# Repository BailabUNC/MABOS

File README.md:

# MABOS
*All work in the MABOS repository is under Copyright Protections enumerated in the LICENSE file. Please contact Arjun Putcha - arjun22@live.unc.edu - for any questions related to redistribution of this work*

*Please see [fastplotlib](https://github.com/kushalkolar/fastplotlib/tree/master), developed by Kushal Kolar, to learn more about the plotting library we primarily use.

https://github.com/BailabUNC/MABOS/assets/96029511/e3c2583f-f5fd-4558-a8c5-83fa992f67cb

There are three key folders in this repository: full_design, firmware, and application.

## Full Design
This folder contains the *CAD* files (.sch and .brd) detailing schematic and layout of our pulse oximeter. It also contains a CAD library file - COMPONENTS_LIB.flbr - that has the relevant files for each component used in our design.

There is also a folder *Fab_Outputs* that contains the fabrication files necessary for laser cutting the top and bottom side of the board. *_autocad.dxf* files contain the file compatible with our laser cutter. Refer to *protocols/PCB_protocols.pdf* to follow our fabrication process.

Below is the schematic for our Infrared LED and Photodiode drivers; The 5-stage analog signal processing pipeline and led drivers are detailed in the schematic. The same schematic is used for the two other channels.

## Firmware
There are 3 directories in this folder: Arduino, Python, and zephyr_workspace.

### Arduino
Contains the .ino file used for the adafruit_itsybitsy_nrf52840 board. The code allows for the control of 3 LED channels and 3 ADC channels. Currently, the duty cycle is set to 50%, and the acquisition rate at 100 Hz.

We also take a burst sample of each ADC (currently 5 samples) to mitigate some noise, and implement a moving average filter with a window size of 10 samples to smooth the output data.

### Python
The code here will soon be removed.

### Zephyr Workspace
Contains the source code, build files, and modified board files to use the adafruit_itsybitsy_nrf52840 board. The board files are modified to configure 3 LED and 3 ADC channels. You can reference the readme file in *firmware/zephyr_workspace* for further details on modifications made.

## Application
The *utils* folder contains the core API used to acquire, plot, and save biosensor data in real time. The *PPG Widget* python notebook utilizes the core API to operate our device. When running this script, a file named *cache.sqlite3* will be created that contains all acquired data. For our uses, we've found a minute of data acquisition corresponds to ~1 MB of data saved.

The *GUI* folder contains a QT Desktop application used solely for displaying acquired biometrics, including SpO2, Heart Rate, Respiration Rate, and Epidermal Melanin Concentration.

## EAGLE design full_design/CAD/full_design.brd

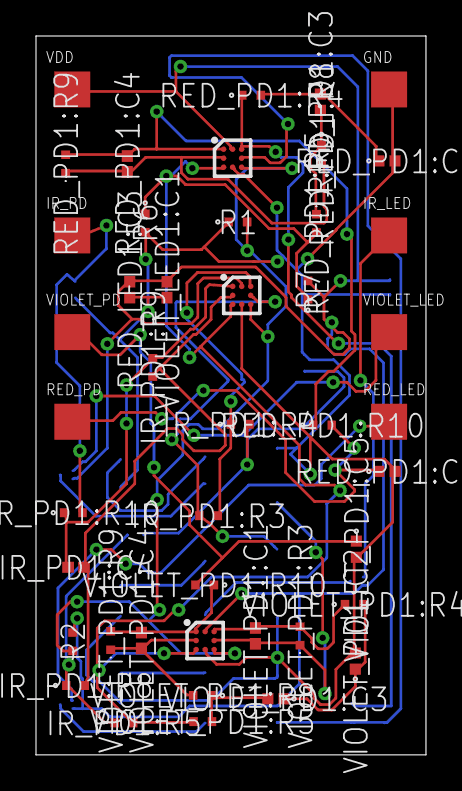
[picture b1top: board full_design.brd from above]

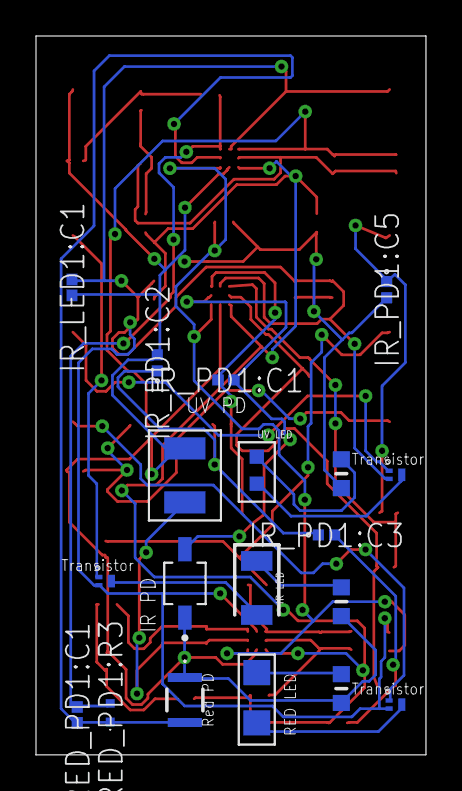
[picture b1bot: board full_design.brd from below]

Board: 2 copper layers, 21.7 x 39.9 mm, 63 parts (19 on the bottom side), 34 nets.

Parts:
GND: PAD
IR_LED: PAD
IR_LED1:C1: CAPACITOR-12PF; CAPC1005X55N
IR_LED1:LED1: IRLED; LEDC3216X180N
IR_LED1:Q1: TRANSISTOR; SOT883B
IR_LED1:R1: RESISTOR-100OHM; RESC1608X55N
IR_PD: PAD
IR_PD1:C1: CAPACITOR-270PF; CAPC1005X55N
IR_PD1:C2, IR_PD1:C5: CAPACITOR-10µF; C0402
IR_PD1:C3: CAPACITOR-3.3µF; C0402
IR_PD1:C4: CAPACITOR-5600PF; CAPC1005X55N
IR_PD1:D1: IRPD; XDCR_VEMD2023X01
IR_PD1:IC1: ADA4505-2; BGA8C50P3X3_142X142X65
IR_PD1:R3, IR_PD1:R9: RESISTOR-4.7MOHM; ERJ2RKD1004X
IR_PD1:R4: RESISTOR-2.7KOHM; ERJPA2_(0402)
IR_PD1:R5: RESISTOR-56KOHM; ERJ2RKD1004X
IR_PD1:R8: RESISTOR-150KOHM; ERJS02_U02_(0402)
IR_PD1:R10: RESISTOR-3.3KOHM; ERJPA2_(0402)
R1: RESISTOR-1.2KOHM; ERJPA2_(0402)
R2: RESISTOR-14KOHM; ERJ2RKD1004X
R6, R7: RESISTOR-3.3KOHM; ERJPA2_(0402)
RED_LED: PAD
RED_LED1:C3: CAPACITOR-12PF; CAPC1005X55N
RED_LED1:Q1: TRANSISTOR; SOT883B
RED_LED1:R5: RESISTOR-100OHM; RESC1608X55N
RED_LED1:U$1: REDLED
RED_PD: PAD
RED_PD1:C1: CAPACITOR-270PF; CAPC1005X55N
RED_PD1:C2, RED_PD1:C5: CAPACITOR-10µF; C0402
RED_PD1:C3: CAPACITOR-3.3µF; C0402
RED_PD1:C4: CAPACITOR-5600PF; CAPC1005X55N
RED_PD1:D1: REDPD; SFH2713
RED_PD1:IC1: ADA4505-2; BGA8C50P3X3_142X142X65
RED_PD1:R3, RED_PD1:R9: RESISTOR-4.7MOHM; ERJ2RKD1004X
RED_PD1:R4: RESISTOR-2.7KOHM; ERJPA2_(0402)
RED_PD1:R5: RESISTOR-56KOHM; ERJ2RKD1004X
RED_PD1:R8: RESISTOR-150KOHM; ERJS02_U02_(0402)
RED_PD1:R10: RESISTOR-3.3KOHM; ERJPA2_(0402)
VDD: PAD
VIOLET_LED: PAD
VIOLET_LED1:C1: CAPACITOR-12PF; CAPC1005X55N
VIOLET_LED1:Q1: TRANSISTOR; SOT883B
VIOLET_LED1:R1: RESISTOR-100OHM; RESC1608X55N
VIOLET_LED1:U$1: UVLED
VIOLET_PD: PAD
VIOLET_PD1:C1: CAPACITOR-270PF; CAPC1005X55N
VIOLET_PD1:C2, VIOLET_PD1:C5: CAPACITOR-10µF; C0402
VIOLET_PD1:C3: CAPACITOR-3.3µF; C0402
VIOLET_PD1:C4: CAPACITOR-5600PF; CAPC1005X55N
VIOLET_PD1:IC1: ADA4505-2; BGA8C50P3X3_142X142X65
VIOLET_PD1:R3, VIOLET_PD1:R9: RESISTOR-4.7MOHM; ERJ2RKD1004X
VIOLET_PD1:R4: RESISTOR-2.7KOHM; ERJPA2_(0402)
VIOLET_PD1:R5: RESISTOR-56KOHM; ERJ2RKD1004X
VIOLET_PD1:R8: RESISTOR-150KOHM; ERJS02_U02_(0402)
VIOLET_PD1:R10: RESISTOR-3.3KOHM; ERJPA2_(0402)
VIOLET_PD1:U$1: UVPD

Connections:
+IN_A_DIV: IR_PD1:IC1.C3, R1.2, R2.1, RED_PD1:IC1.C3, VIOLET_PD1:IC1.C3
+IN_B_DIV: IR_PD1:IC1.C1, IR_PD1:R5.2, R6.1, R7.1, RED_PD1:IC1.C1, RED_PD1:R5.2, VIOLET_PD1:IC1.C1, VIOLET_PD1:R5.2
GND: GND.PAD, IR_LED1:C1.1, IR_LED1:R1.1, IR_PD1:C2.2, IR_PD1:C5.2, IR_PD1:D1.C, IR_PD1:IC1.C2, R1.1, R6.2, RED_LED1:C3.1, RED_LED1:R5.1, RED_PD1:C2.2, RED_PD1:C5.2, RED_PD1:D1.1, RED_PD1:IC1.C2, VIOLET_LED1:C1.1, VIOLET_LED1:R1.1, VIOLET_PD1:C2.2, VIOLET_PD1:C5.2, VIOLET_PD1:IC1.C2, VIOLET_PD1:U$1.OUT
IR_LED1:N$1: IR_LED1:LED1.1, IR_LED1:R1.2
IR_LED1:N$4: IR_LED1:LED1.2, IR_LED1:Q1.3
IR_PD1:-IN_A_I: IR_PD1:C1.1, IR_PD1:D1.A, IR_PD1:IC1.B3, IR_PD1:R3.1
IR_PD1:-IN_B_I: IR_PD1:C4.1, IR_PD1:IC1.B1, IR_PD1:R8.2, IR_PD1:R9.1
IR_PD1:N$5: IR_PD1:C2.1, IR_PD1:C3.1, IR_PD1:R4.2
IR_PD1:N$7: IR_PD1:C3.2, IR_PD1:R5.1, IR_PD1:R8.1
IR_PD1:OUT_A_I: IR_PD1:C1.2, IR_PD1:IC1.A3, IR_PD1:R3.2, IR_PD1:R4.1
IR_PD1:OUT_B_I: IR_PD1:C4.2, IR_PD1:IC1.A1, IR_PD1:R9.2, IR_PD1:R10.1
unnamed: RED_PD.PAD, RED_PD1:C5.1, RED_PD1:R10.2
unnamed: RED_LED.PAD, RED_LED1:Q1.1
unnamed: IR_LED.PAD, IR_LED1:Q1.1
unnamed: VIOLET_LED.PAD, VIOLET_LED1:Q1.1
unnamed: VIOLET_PD.PAD, VIOLET_PD1:C5.1, VIOLET_PD1:R10.2
unnamed: IR_PD.PAD, IR_PD1:C5.1, IR_PD1:R10.2
RED_LED1:N$7: RED_LED1:Q1.3, RED_LED1:U$1.IN
RED_LED1:N$13: RED_LED1:R5.2, RED_LED1:U$1.OUT
RED_PD1:-IN_A_R: RED_PD1:C1.1, RED_PD1:D1.2, RED_PD1:IC1.B3, RED_PD1:R3.1
RED_PD1:-IN_B_R: RED_PD1:C4.1, RED_PD1:IC1.B1, RED_PD1:R8.2, RED_PD1:R9.1
RED_PD1:N$1: RED_PD1:C2.1, RED_PD1:C3.1, RED_PD1:R4.2
RED_PD1:N$3: RED_PD1:C3.2, RED_PD1:R5.1, RED_PD1:R8.1
RED_PD1:OUT_A_R: RED_PD1:C1.2, RED_PD1:IC1.A3, RED_PD1:R3.2, RED_PD1:R4.1
RED_PD1:OUT_B_R: RED_PD1:C4.2, RED_PD1:IC1.A1, RED_PD1:R9.2, RED_PD1:R10.1
VDD: IR_LED1:C1.2, IR_LED1:Q1.2, IR_PD1:IC1.A2, R2.2, R7.2, RED_LED1:C3.2, RED_LED1:Q1.2, RED_PD1:IC1.A2, VDD.PAD, VIOLET_LED1:C1.2, VIOLET_LED1:Q1.2, VIOLET_PD1:IC1.A2
VIOLET_LED1:N$1: VIOLET_LED1:R1.2, VIOLET_LED1:U$1.OUT
VIOLET_LED1:N$2: VIOLET_LED1:Q1.3, VIOLET_LED1:U$1.IN
VIOLET_PD1:-IN_A_V: VIOLET_PD1:C1.1, VIOLET_PD1:IC1.B3, VIOLET_PD1:R3.1, VIOLET_PD1:U$1.IN
VIOLET_PD1:-IN_B_V: VIOLET_PD1:C4.1, VIOLET_PD1:IC1.B1, VIOLET_PD1:R8.2, VIOLET_PD1:R9.1
VIOLET_PD1:N$5: VIOLET_PD1:C2.1, VIOLET_PD1:C3.1, VIOLET_PD1:R4.2
VIOLET_PD1:N$7: VIOLET_PD1:C3.2, VIOLET_PD1:R5.1, VIOLET_PD1:R8.1
VIOLET_PD1:OUT_A_V: VIOLET_PD1:C1.2, VIOLET_PD1:IC1.A3, VIOLET_PD1:R3.2, VIOLET_PD1:R4.1
VIOLET_PD1:OUT_B_V: VIOLET_PD1:C4.2, VIOLET_PD1:IC1.A1, VIOLET_PD1:R9.2, VIOLET_PD1:R10.1

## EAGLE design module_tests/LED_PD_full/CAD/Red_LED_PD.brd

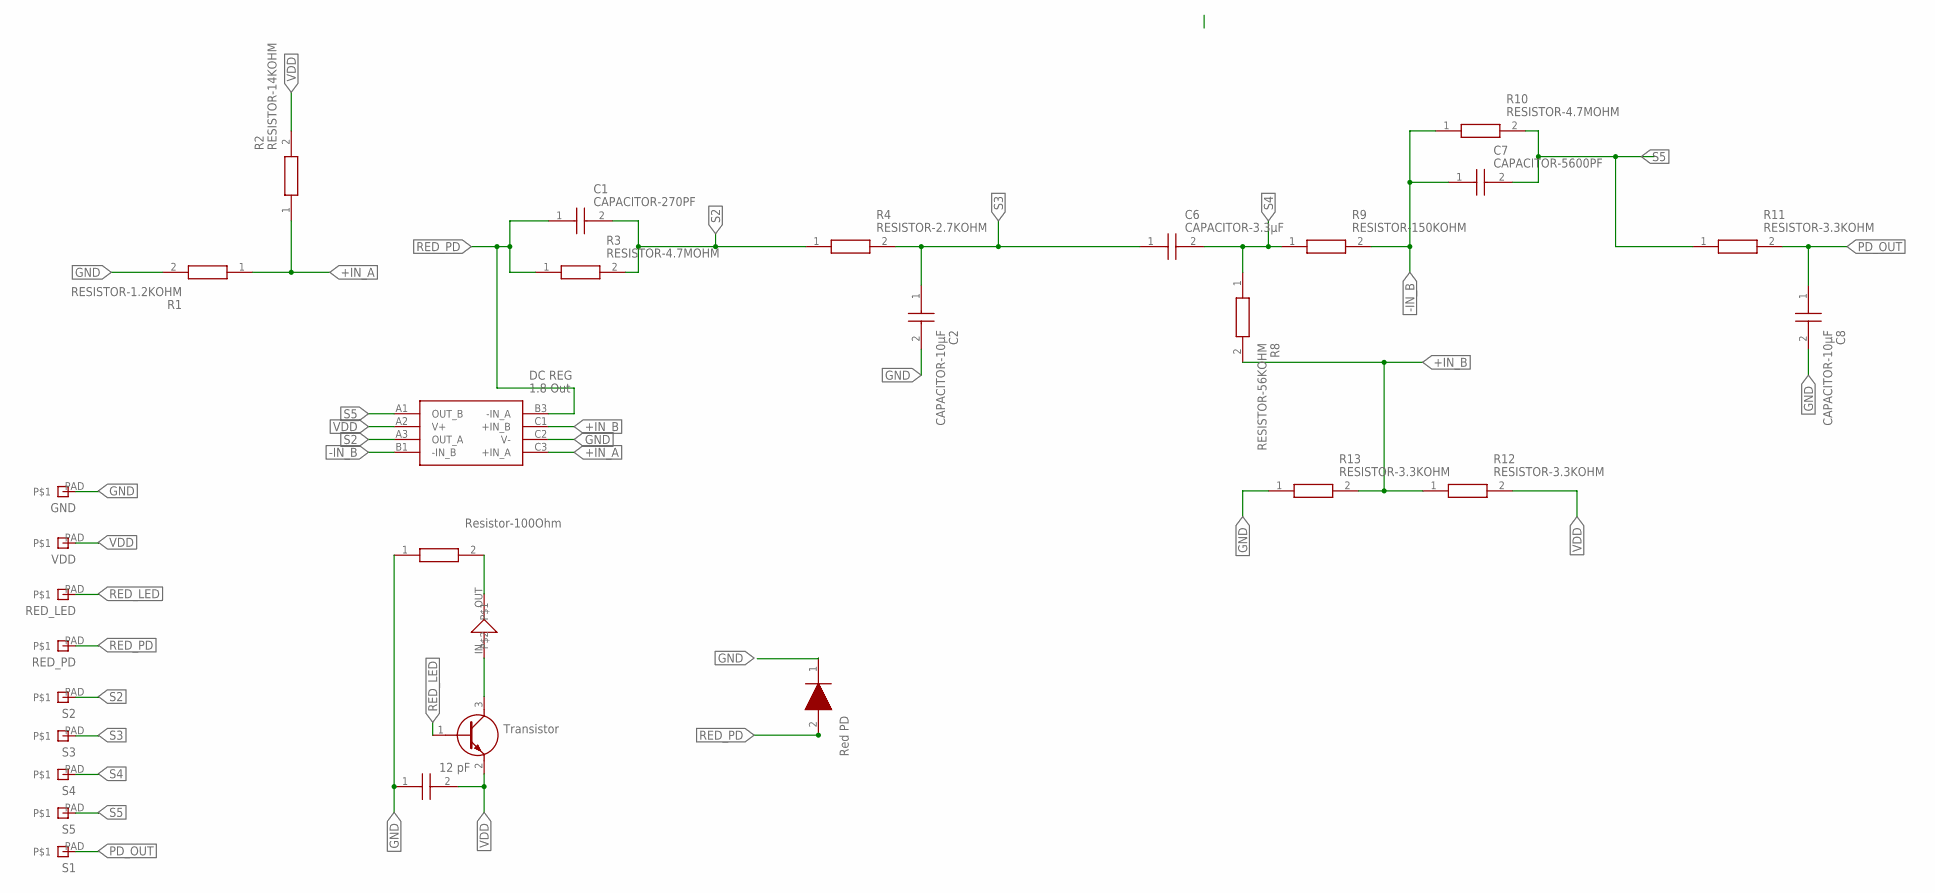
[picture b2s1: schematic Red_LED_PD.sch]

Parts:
C1: CAPACITOR-270PF; CAPC1005X55N@1
C2, C8: CAPACITOR-10µF; C0402
C3: CAPACITOR-12PF; CAPC1005X55N
C6: CAPACITOR-3.3µF; C0402
C7: CAPACITOR-5600PF; CAPC1005X55N@1
D1: REDPD; SFH2713
GND: PAD
IC1: ADA4505-2; BGA8C50P3X3_142X142X65
Q1: TRANSISTOR; SOT883B
R1: RESISTOR-1.2KOHM; ERJPA2_(0402)
R2: RESISTOR-14KOHM; ERJ2RKD1004X
R3, R10: RESISTOR-4.7MOHM; ERJ2RKD1004X
R4: RESISTOR-2.7KOHM; ERJPA2_(0402)
R5: RESISTOR-100OHM; RESC1608X55N
R8: RESISTOR-56KOHM; ERJ2RKD1004X
R9: RESISTOR-150KOHM; ERJS02_U02_(0402)
R11, R12, R13: RESISTOR-3.3KOHM; ERJPA2_(0402)
RED_LED: PAD
RED_PD: PAD
S1, S2, S3, S4, S5: PAD
U$1: REDLED
VDD: PAD

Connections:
+IN_A: IC1.C3 (+IN_A), R1.1, R2.1
+IN_B: IC1.C1 (+IN_B), R8.2, R12.1, R13.2
-IN_B: C7.1, IC1.B1 (-IN_B), R9.2, R10.1
GND: C2.2, C3.1, C8.2, D1.1 (K), GND.PAD, IC1.C2 (V-), R1.2, R5.1, R13.1
unnamed: Q1.3 (C), U$1.IN
unnamed: R5.2, U$1.OUT
PD_OUT: C8.1, R11.2, S1.PAD
RED_LED: Q1.1 (B), RED_LED.PAD
RED_PD: C1.1, D1.2 (A), IC1.B3 (-IN_A), R3.1, RED_PD.PAD
S2: C1.2, IC1.A3 (OUT_A), R3.2, R4.1, S2.PAD
S3: C2.1, C6.1, R4.2, S3.PAD
S4: C6.2, R8.1, R9.1, S4.PAD
S5: C7.2, IC1.A1 (OUT_B), R10.2, R11.1, S5.PAD
VDD: C3.2, IC1.A2 (V+), Q1.2 (E), R2.2, R12.2, VDD.PAD

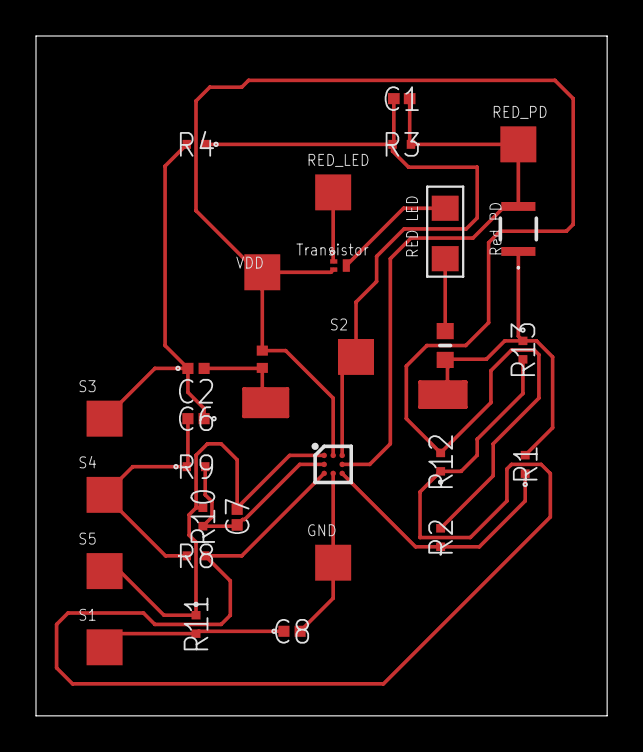
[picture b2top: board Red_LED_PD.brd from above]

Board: 2 copper layers, 31.7 x 37.8 mm, 30 parts (0 on the bottom side), 14 nets.

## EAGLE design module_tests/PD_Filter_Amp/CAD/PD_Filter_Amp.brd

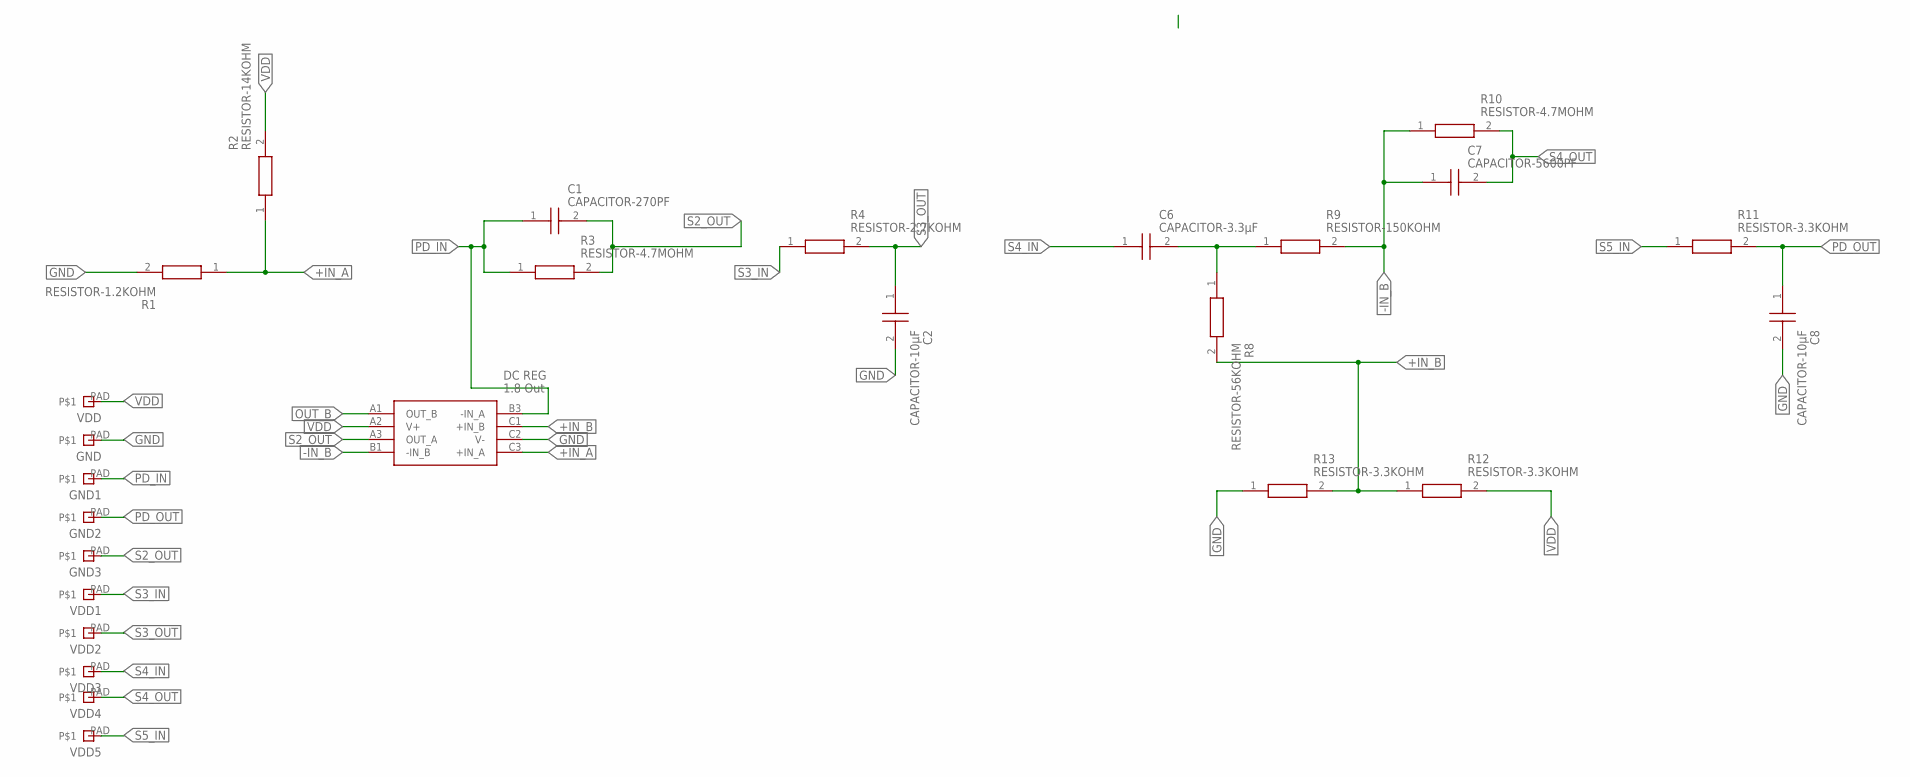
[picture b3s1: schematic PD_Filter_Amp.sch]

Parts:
C1: CAPACITOR-270PF; CAPC1005X55N
C2, C8: CAPACITOR-10µF; C0402
C6: CAPACITOR-3.3µF; C0402
C7: CAPACITOR-5600PF; CAPC1005X55N
GND, GND1, GND2, GND3: PAD
IC1: ADA4505-2; BGA8C50P3X3_142X142X65
R1: RESISTOR-1.2KOHM; ERJPA2_(0402)
R2: RESISTOR-14KOHM; ERJ2RKD1004X
R3, R10: RESISTOR-4.7MOHM; ERJ2RKD1004X
R4: RESISTOR-2.7KOHM; ERJPA2_(0402)
R8: RESISTOR-56KOHM; ERJ2RKD1004X
R9: RESISTOR-150KOHM; ERJS02_U02_(0402)
R11, R12, R13: RESISTOR-3.3KOHM; ERJPA2_(0402)
VDD, VDD1, VDD2, VDD3, VDD4, VDD5: PAD

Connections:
+IN_A: IC1.C3 (+IN_A), R1.1, R2.1
+IN_B: IC1.C1 (+IN_B), R8.2, R12.1, R13.2
-IN_B: C7.1, IC1.B1 (-IN_B), R9.2, R10.1
GND: C2.2, C8.2, GND.PAD, IC1.C2 (V-), R1.2, R13.1
unnamed: C6.2, R8.1, R9.1
OUT_B: IC1.A1 (OUT_B)
PD_IN: C1.1, GND1.PAD, IC1.B3 (-IN_A), R3.1
PD_OUT: C8.1, GND2.PAD, R11.2
S2_OUT: C1.2, GND3.PAD, IC1.A3 (OUT_A), R3.2
S3_IN: R4.1, VDD1.PAD
S3_OUT: C2.1, R4.2, VDD2.PAD
S4_IN: C6.1, VDD3.PAD
S4_OUT: C7.2, R10.2, VDD4.PAD
S5_IN: R11.1, VDD5.PAD
VDD: IC1.A2 (V+), R2.2, R12.2, VDD.PAD

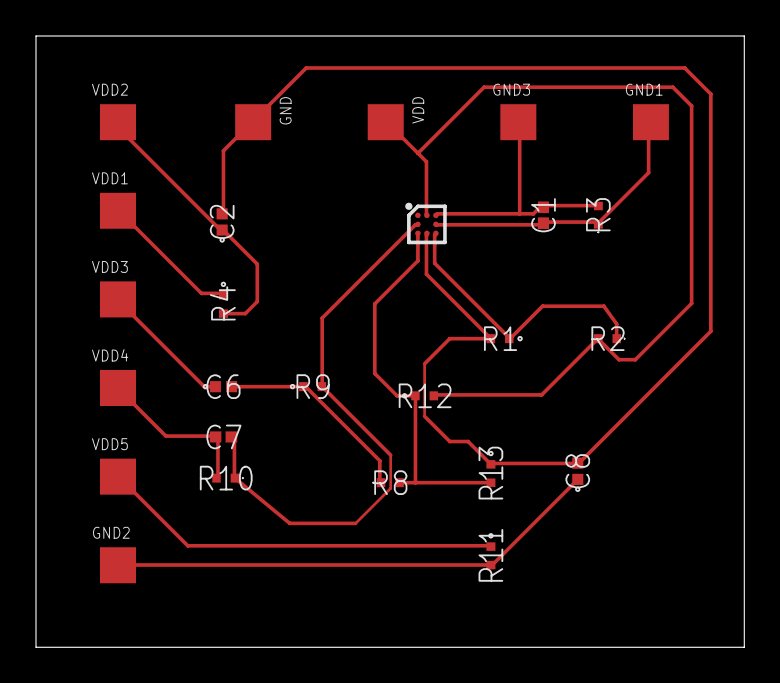
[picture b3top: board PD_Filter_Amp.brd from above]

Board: 2 copper layers, 39.4 x 34.0 mm, 26 parts (0 on the bottom side), 14 nets.

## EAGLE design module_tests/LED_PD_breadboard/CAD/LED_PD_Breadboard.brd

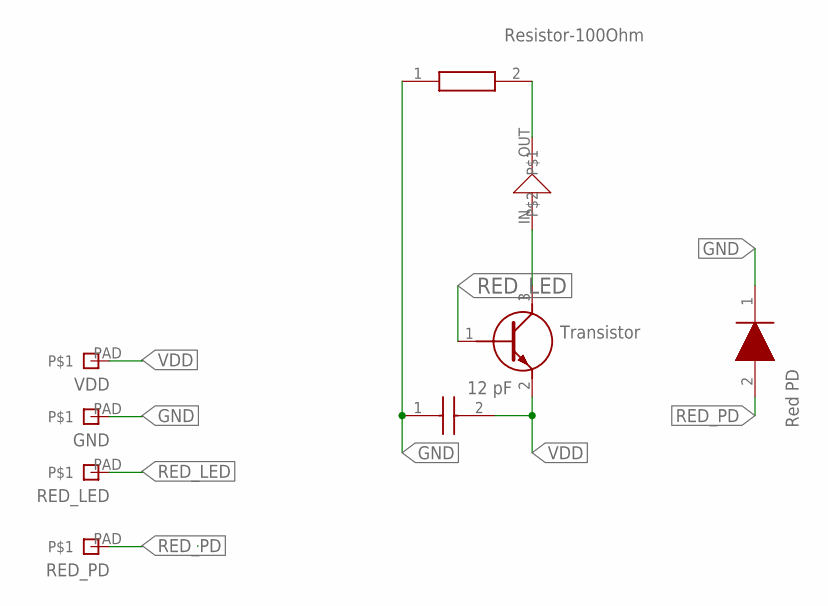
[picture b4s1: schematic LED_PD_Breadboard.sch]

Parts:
C1: CAPACITOR-12PF; CAPC1005X55N
D1: REDPD; SFH2713
GND: PAD
Q1: TRANSISTOR; SOT883B
R1: RESISTOR-100OHM; RESC1608X55N
RED_LED: PAD
RED_PD: PAD
U$1: REDLED
VDD: PAD

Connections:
GND: C1.1, D1.1 (K), GND.PAD, R1.1
unnamed: Q1.3 (C), U$1.IN
unnamed: R1.2, U$1.OUT
RED_LED: Q1.1 (B), RED_LED.PAD
RED_PD: D1.2 (A), RED_PD.PAD
VDD: C1.2, Q1.2 (E), VDD.PAD

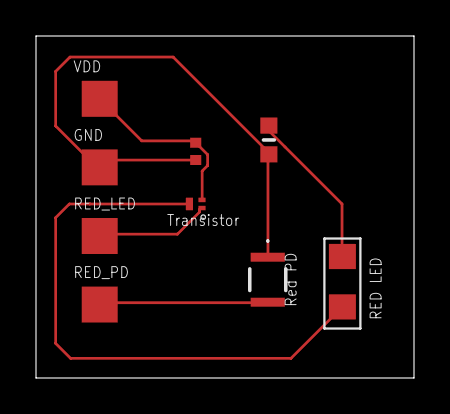
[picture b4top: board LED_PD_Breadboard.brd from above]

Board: 2 copper layers, 21.0 x 19.0 mm, 9 parts (0 on the bottom side), 6 nets.

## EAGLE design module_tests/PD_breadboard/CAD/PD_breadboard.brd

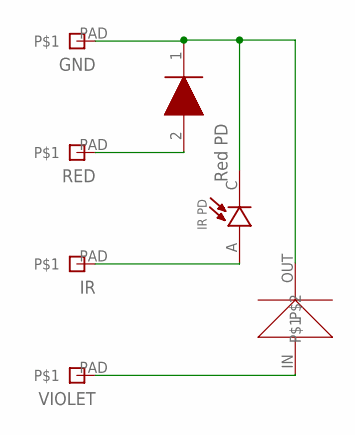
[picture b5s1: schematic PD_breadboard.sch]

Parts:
D1: REDPD; SFH2713
D2: IRPD; XDCR_VEMD2023X01
GND: PAD
IR: PAD
RED: PAD
U$1: UVPD
VIOLET: PAD

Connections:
unnamed: D1.2 (A), RED.PAD
unnamed: D1.1 (K), D2.C, GND.PAD, U$1.OUT
unnamed: D2.A, IR.PAD
unnamed: U$1.IN, VIOLET.PAD

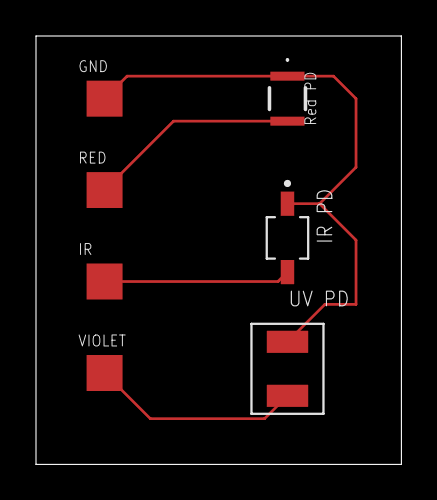
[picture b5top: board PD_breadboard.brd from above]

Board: 2 copper layers, 20.3 x 23.8 mm, 7 parts (0 on the bottom side), 4 nets.

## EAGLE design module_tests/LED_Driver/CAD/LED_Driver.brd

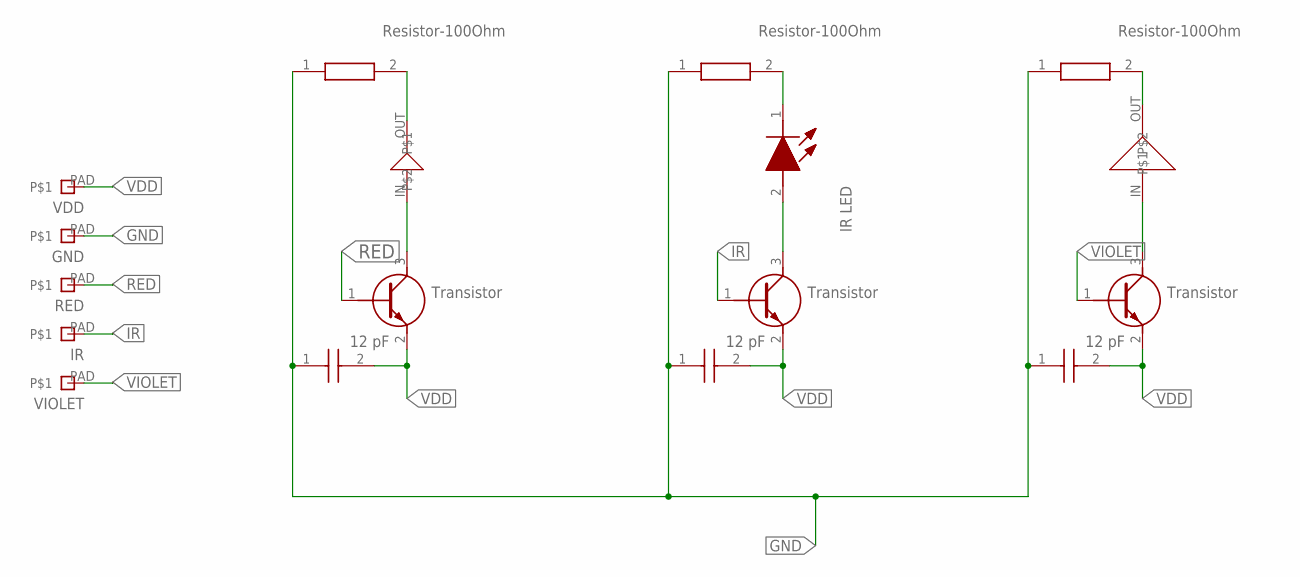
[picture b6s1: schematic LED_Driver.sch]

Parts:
C1, C3, C5: CAPACITOR-12PF; CAPC1005X55N
GND: PAD
IR: PAD
LED1: IRLED; LEDC3216X180N
Q1, Q3, Q5: TRANSISTOR; SOT883B
R1, R3, R5: RESISTOR-100OHM; RESC1608X55N
RED: PAD
U$1: REDLED
U$3: UVLED
VDD: PAD
VIOLET: PAD

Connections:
GND: C1.1, C3.1, C5.1, GND.PAD, R1.1, R3.1, R5.1
IR: IR.PAD, Q3.1 (B)
unnamed: Q1.3 (C), U$1.IN
unnamed: LED1.2 (A), Q3.3 (C)
unnamed: Q5.3 (C), U$3.IN
unnamed: R1.2, U$1.OUT
unnamed: LED1.1 (K), R3.2
unnamed: R5.2, U$3.OUT
RED: Q1.1 (B), RED.PAD
VDD: C1.2, C3.2, C5.2, Q1.2 (E), Q3.2 (E), Q5.2 (E), VDD.PAD
VIOLET: Q5.1 (B), VIOLET.PAD

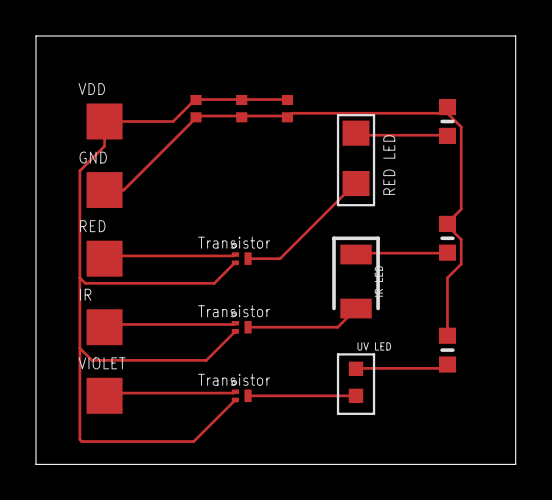
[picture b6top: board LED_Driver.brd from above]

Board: 2 copper layers, 26.6 x 23.8 mm, 17 parts (0 on the bottom side), 11 nets.

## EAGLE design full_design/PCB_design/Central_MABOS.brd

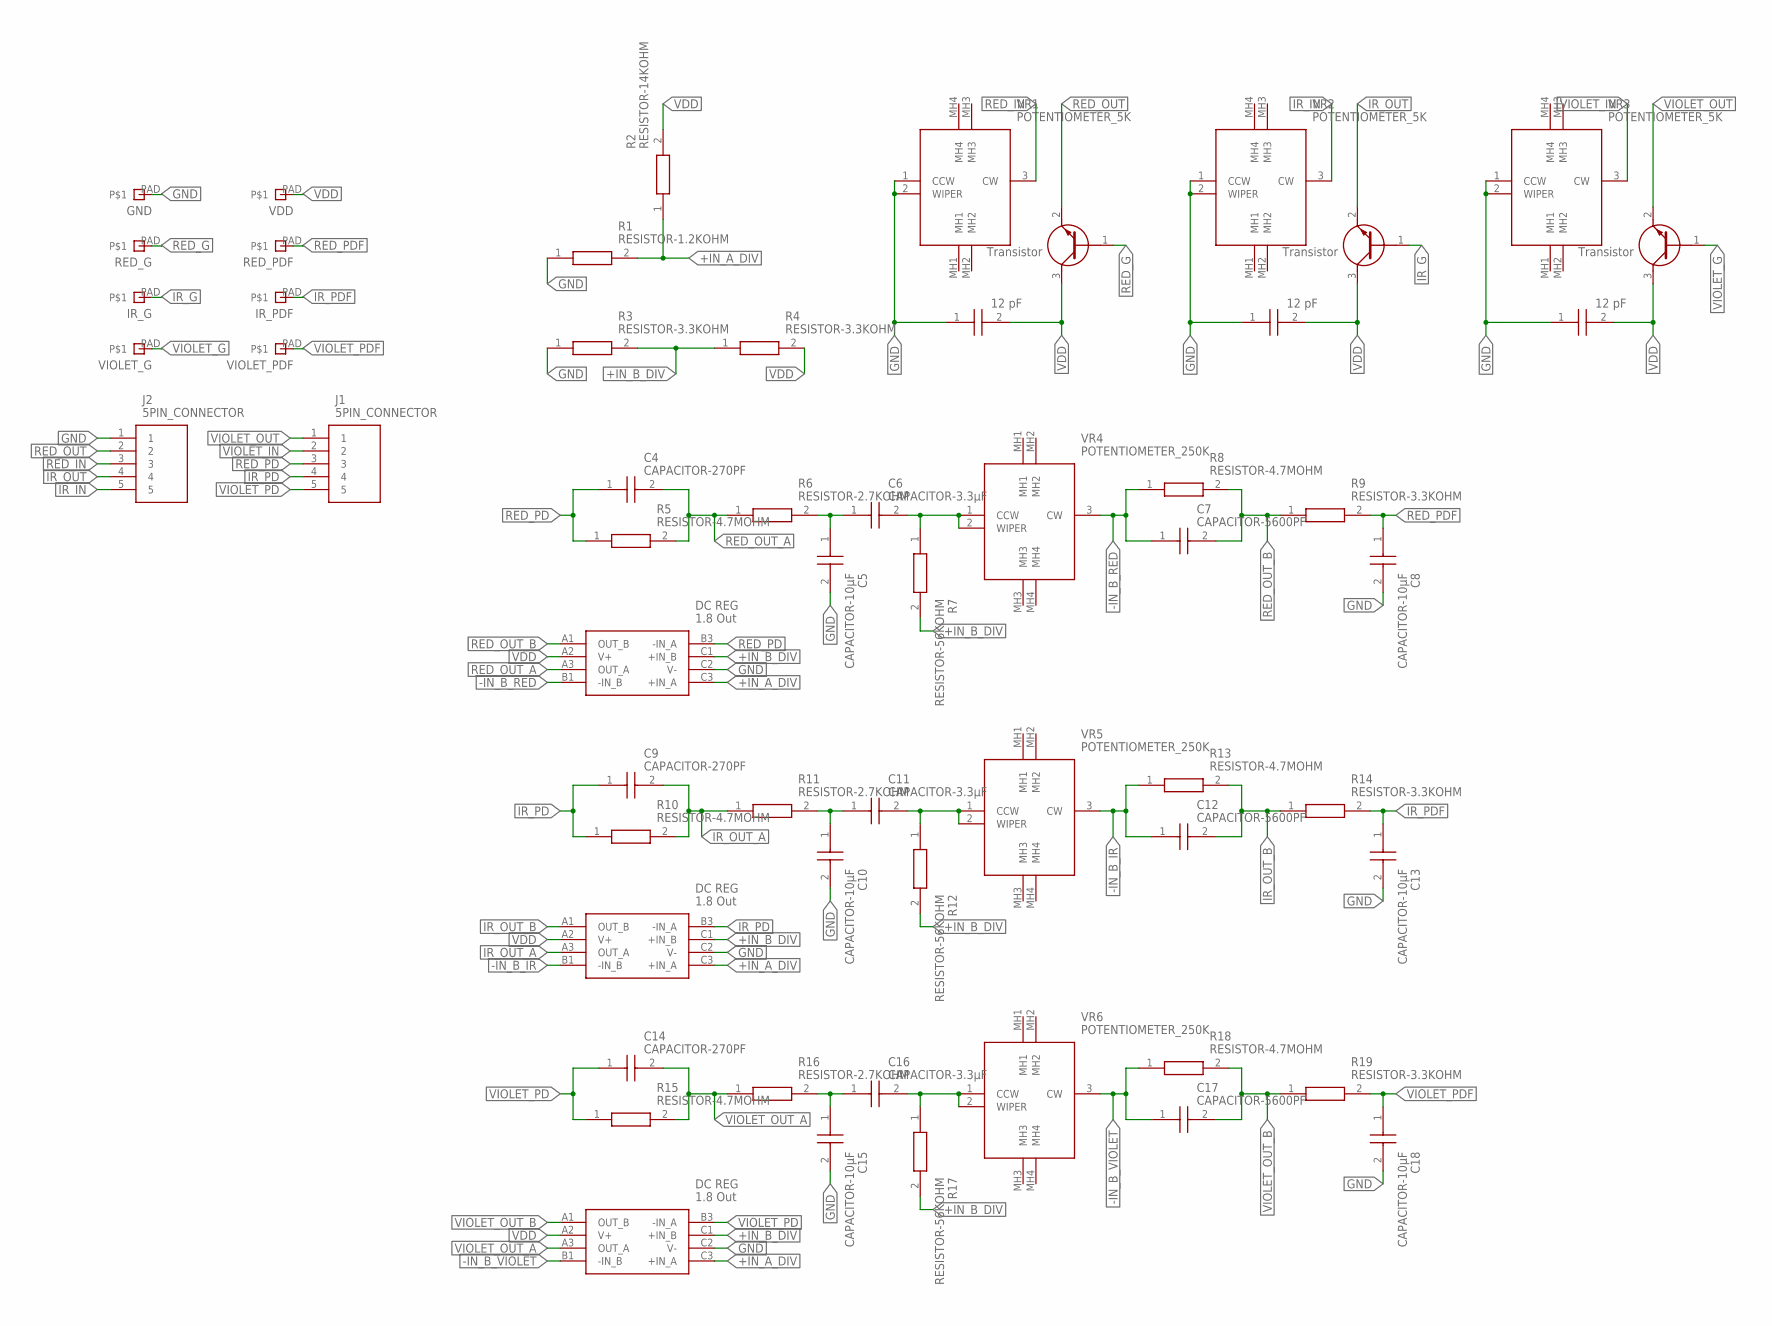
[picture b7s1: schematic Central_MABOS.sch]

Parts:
C1, C2, C3: CAPACITOR-12PF; CAPC1005X55N
C4, C9, C14: CAPACITOR-270PF; CAPC1005X55N
C5, C8, C10, C13, C15, C18: CAPACITOR-10µF; C0402
C6, C11, C16: CAPACITOR-3.3µF; C0402
C7, C12, C17: CAPACITOR-5600PF; CAPC1005X55N
GND: PAD
IC1, IC2, IC3: ADA4505-2; BGA8C50P3X3_142X142X65
IR_G: PAD
IR_PDF: PAD
J1, J2: 5PIN_CONNECTOR; SHDR5W114P0X419_1X5_2228X658X1
Q1, Q2, Q3: TRANSISTOR; SOT883B
R1: RESISTOR-1.2KOHM; ERJPA2_(0402)
R2: RESISTOR-14KOHM; ERJ2RKD1004X
R3, R4, R9, R14, R19: RESISTOR-3.3KOHM; ERJPA2_(0402)
R5, R8, R10, R13, R15, R18: RESISTOR-4.7MOHM; ERJ2RKD1004X
R6, R11, R16: RESISTOR-2.7KOHM; ERJPA2_(0402)
R7, R12, R17: RESISTOR-56KOHM; ERJ2RKD1004X
RED_G: PAD
RED_PDF: PAD
VDD: PAD
VIOLET_G: PAD
VIOLET_PDF: PAD
VR1, VR2, VR3: POTENTIOMETER_5K; POTENTIOMETER
VR4, VR5, VR6: POTENTIOMETER_250K; PTA60432015DPB254

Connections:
+IN_A_DIV: IC1.C3 (+IN_A), IC2.C3 (+IN_A), IC3.C3 (+IN_A), R1.2, R2.1
+IN_B_DIV: IC1.C1 (+IN_B), IC2.C1 (+IN_B), IC3.C1 (+IN_B), R3.2, R4.1, R7.2, R12.2, R17.2
-IN_B_IR: C12.1, IC2.B1 (-IN_B), R13.1, VR5.3 (CW)
-IN_B_RED: C7.1, IC1.B1 (-IN_B), R8.1, VR4.3 (CW)
-IN_B_VIOLET: C17.1, IC3.B1 (-IN_B), R18.1, VR6.3 (CW)
GND: C1.1, C2.1, C3.1, C5.2, C8.2, C10.2, C13.2, C15.2, C18.2, GND.PAD, IC1.C2 (V-), IC2.C2 (V-), IC3.C2 (V-), J2.1, R1.1, R3.1, VR1.1 (CCW), VR1.2 (WIPER), VR2.1 (CCW), VR2.2 (WIPER), VR3.1 (CCW), VR3.2 (WIPER)
IR_G: IR_G.PAD, Q2.1 (B)
IR_IN: J2.5, VR2.3 (CW)
IR_OUT: J2.4, Q2.2 (E)
IR_OUT_A: C9.2, IC2.A3 (OUT_A), R10.2, R11.1
IR_OUT_B: C12.2, IC2.A1 (OUT_B), R13.2, R14.1
IR_PD: C9.1, IC2.B3 (-IN_A), J1.4, R10.1
IR_PDF: C13.1, IR_PDF.PAD, R14.2
unnamed: C5.1, C6.1, R6.2
unnamed: C6.2, R7.1, VR4.1 (CCW), VR4.2 (WIPER)
unnamed: C10.1, C11.1, R11.2
unnamed: C11.2, R12.1, VR5.1 (CCW), VR5.2 (WIPER)
unnamed: C15.1, C16.1, R16.2
unnamed: C16.2, R17.1, VR6.1 (CCW), VR6.2 (WIPER)
RED_G: Q1.1 (B), RED_G.PAD
RED_IN: J2.3, VR1.3 (CW)
RED_OUT: J2.2, Q1.2 (E)
RED_OUT_A: C4.2, IC1.A3 (OUT_A), R5.2, R6.1
RED_OUT_B: C7.2, IC1.A1 (OUT_B), R8.2, R9.1
RED_PD: C4.1, IC1.B3 (-IN_A), J1.3, R5.1
RED_PDF: C8.1, R9.2, RED_PDF.PAD
VDD: C1.2, C2.2, C3.2, IC1.A2 (V+), IC2.A2 (V+), IC3.A2 (V+), Q1.3 (C), Q2.3 (C), Q3.3 (C), R2.2, R4.2, VDD.PAD
VIOLET_G: Q3.1 (B), VIOLET_G.PAD
VIOLET_IN: J1.2, VR3.3 (CW)
VIOLET_OUT: J1.1, Q3.2 (E)
VIOLET_OUT_A: C14.2, IC3.A3 (OUT_A), R15.2, R16.1
VIOLET_OUT_B: C17.2, IC3.A1 (OUT_B), R18.2, R19.1
VIOLET_PD: C14.1, IC3.B3 (-IN_A), J1.5, R15.1
VIOLET_PDF: C18.1, R19.2, VIOLET_PDF.PAD

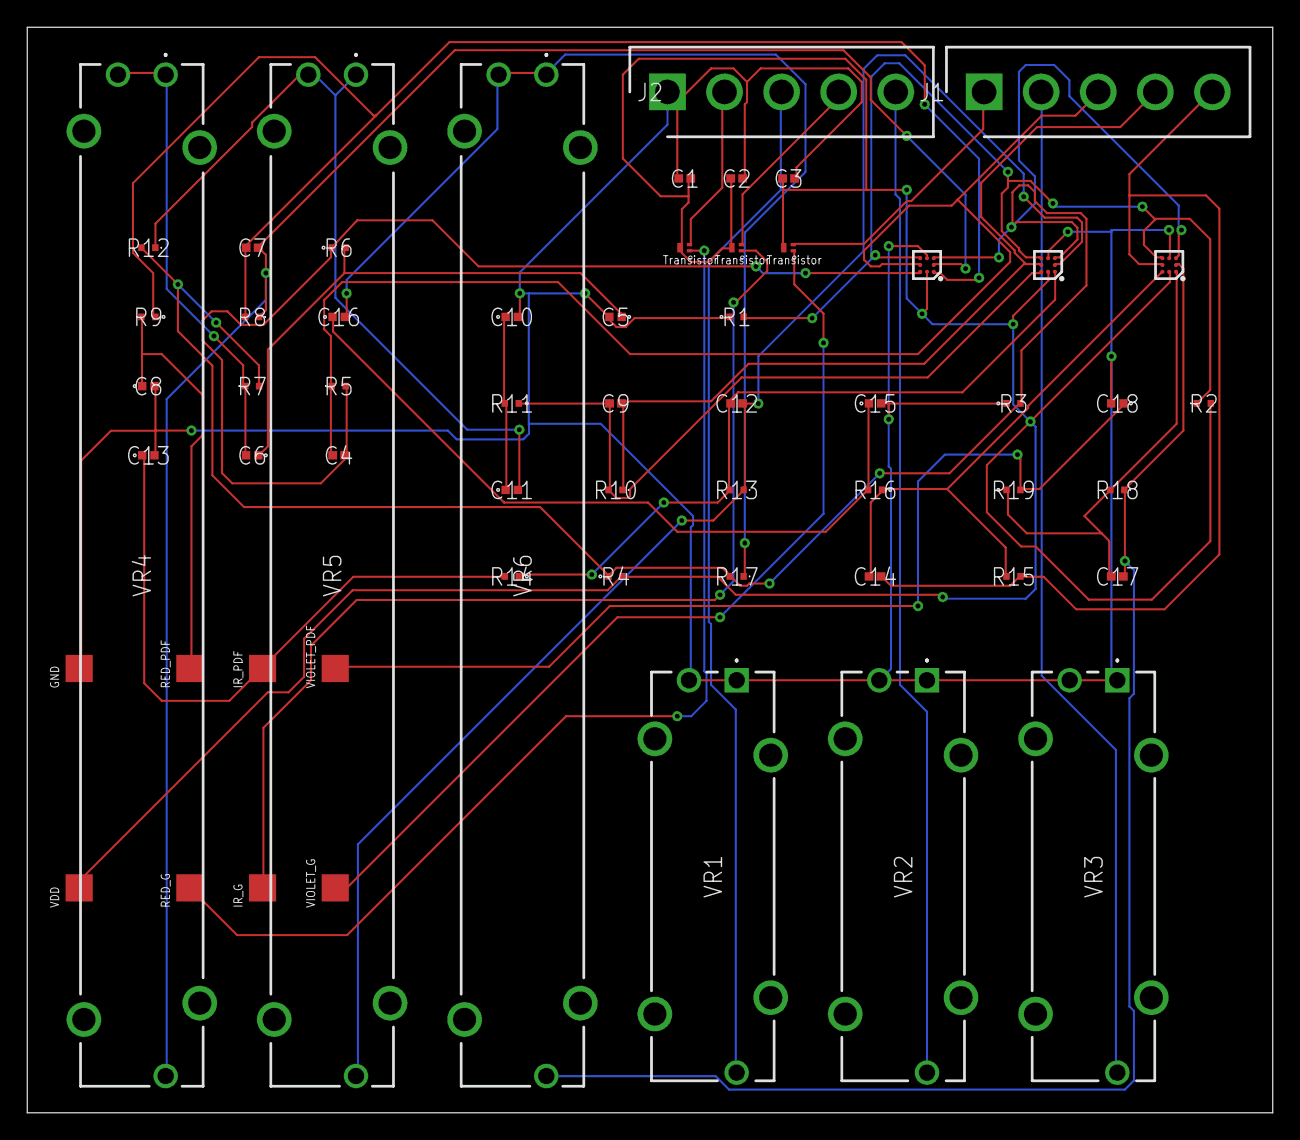
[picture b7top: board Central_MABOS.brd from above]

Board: 2 copper layers, 91.4 x 79.7 mm, 59 parts (0 on the bottom side), 34 nets.

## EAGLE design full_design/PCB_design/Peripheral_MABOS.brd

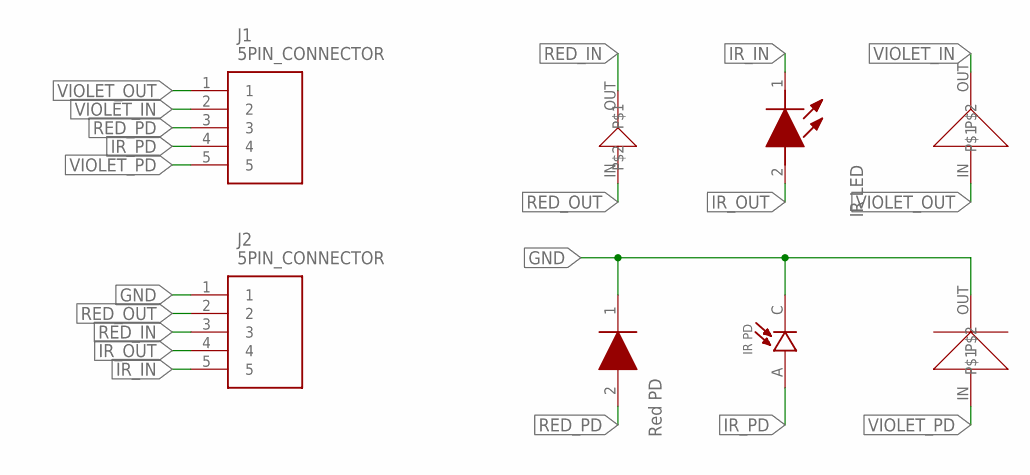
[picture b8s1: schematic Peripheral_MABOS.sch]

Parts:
D1: REDPD; SFH2713
D2: IRPD; XDCR_VEMD2023X01
J1, J2: 5PIN_CONNECTOR; SHDR5W114P0X419_1X5_2228X658X1
LED1: IRLED; LEDC3216X180N
U$1: REDLED
U$2: UVLED
U$3: UVPD

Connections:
GND: D1.1 (K), D2.C, J2.1, U$3.OUT
IR_IN: J2.5, LED1.1 (K)
IR_OUT: J2.4, LED1.2 (A)
IR_PD: D2.A, J1.4
RED_IN: J2.3, U$1.OUT
RED_OUT: J2.2, U$1.IN
RED_PD: D1.2 (A), J1.3
VIOLET_IN: J1.2, U$2.OUT
VIOLET_OUT: J1.1, U$2.IN
VIOLET_PD: J1.5, U$3.IN

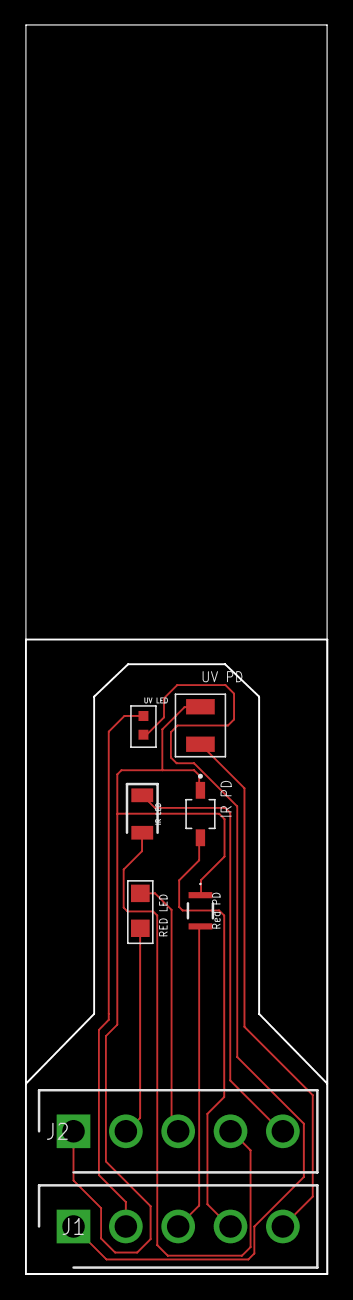
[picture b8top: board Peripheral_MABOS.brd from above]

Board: 2 copper layers, 24.1 x 100.0 mm, 8 parts (0 on the bottom side), 10 nets.

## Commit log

2023-04-10 LED_Driver Module added
2023-04-12 Add module test for PD filter/amp circuit on breadboard. Will upload schematic of filtering circuit later
2023-04-21 LED-PD module test
2023-05-02 Schematic of filtering circuit
2023-05-04 add components library
2023-05-04 updated components library. Added schematic for filter/amp circuit
2023-05-05 Add schematic & layout for filter_amplification circuit
2023-05-05 reorganize module_tests folder
2023-05-08 modified filter/amp circuit fab
2023-05-09 UNC License
2023-05-09 fixed bug in filter circuit, added test points between each stage
2023-05-15 led pd full circuit
2023-05-16 fabrication files for led-pd full circuit
2023-05-28 initial python firmware
2023-05-29 python code for parallelized real-time plotting data via fastplotlib
2023-05-29 arduino base firmware code
2023-05-30 add autoscale feature for y axis
2023-05-30 reformat arduino folder
2023-05-30 initial attempt at moving average filter with burst sampling
2023-05-30 oops now i fixed it
2023-05-30 adding burst sampling and moving average filter
2023-06-01 schematic and layout for full oximeter
2023-06-01 fabrication files for top/bottom of pcb?
2023-06-01 application skeleton
2023-06-01 remove references to mpl
2023-06-05 move core functionality of MABOS API to utils folder, set up groundwork for web and desktop GUI
2023-06-06 trial 2 at using MABOS-core API for web-based GUI. Issue coordinating processes
2023-06-07 core API works with jupyter notebook now
2023-06-09 updated application to handle 3 channel data acquisition
2023-06-09 plots are in rows, auto-scaling added
2023-06-09 modify firmware to handle 3 channels, 100 Hz, 50% duty cycle
2023-06-09 add notebook for plotting using MABOS-core utils
2023-06-09 small changes
2023-06-12 added module to continuously save data to disk
2023-06-12 update license
2023-06-12 update readme, remove license primary
2023-06-12 fix name license file
2023-06-23 add ability for user to customize number of channels
2023-06-27 add class manager to handle plotting and processing. Only user input is num channels, ser port, and baudrate if needed
2023-06-27 forgot to add central manager
2023-06-27 pass args in dictionary to key processes
2023-06-27 zephyr-based code for benchtop test
2023-06-28 added UART support
2023-06-29 moving core API to separate repo
2023-06-29 move module tests to resources repo
2023-06-29 modified ppg widget
2023-06-29 calls MABOS-core now
2023-07-03 modified code to work with new mabos core
2023-07-12 Update README.md with video
2023-07-12 Update README.md update video
2023-07-18 updates to schematic docs
2023-07-25 change LED pin output
2023-07-25 3d print file for light blocker
2023-07-26 updated file names
2023-08-01 Update library files
2023-08-23 added 3D printing file for full casing
2023-10-19 update component libraries to include connector and rheostat
2023-10-19 add more potentiometers for tuning ASP
2023-10-23 switch to modular design of mabos. central handles ASP and addes rheometer for LED brightness and ASP gain control. Peripheral has LED/PD array
2023-11-15 modified filenames and updated casing design
